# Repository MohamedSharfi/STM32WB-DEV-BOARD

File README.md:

# STM32 Development Breadboard Prototype 
This repository contains the schematic, PCB design, and documentation for an STM32-based development prototype designed for breadboard testing and prototyping.

## Project Status
     Schematic    :  100% Complete
     PCB Design   :  100% Complete
     Documentation:  100% Complete

## Table of Contents
Overview
Features
Getting Started
Project Files
Documentation
Contributing
License
Overview
This project aims to provide a robust STM32 development environment optimized for breadboard prototyping. It's ideal for my next projects development & testing.

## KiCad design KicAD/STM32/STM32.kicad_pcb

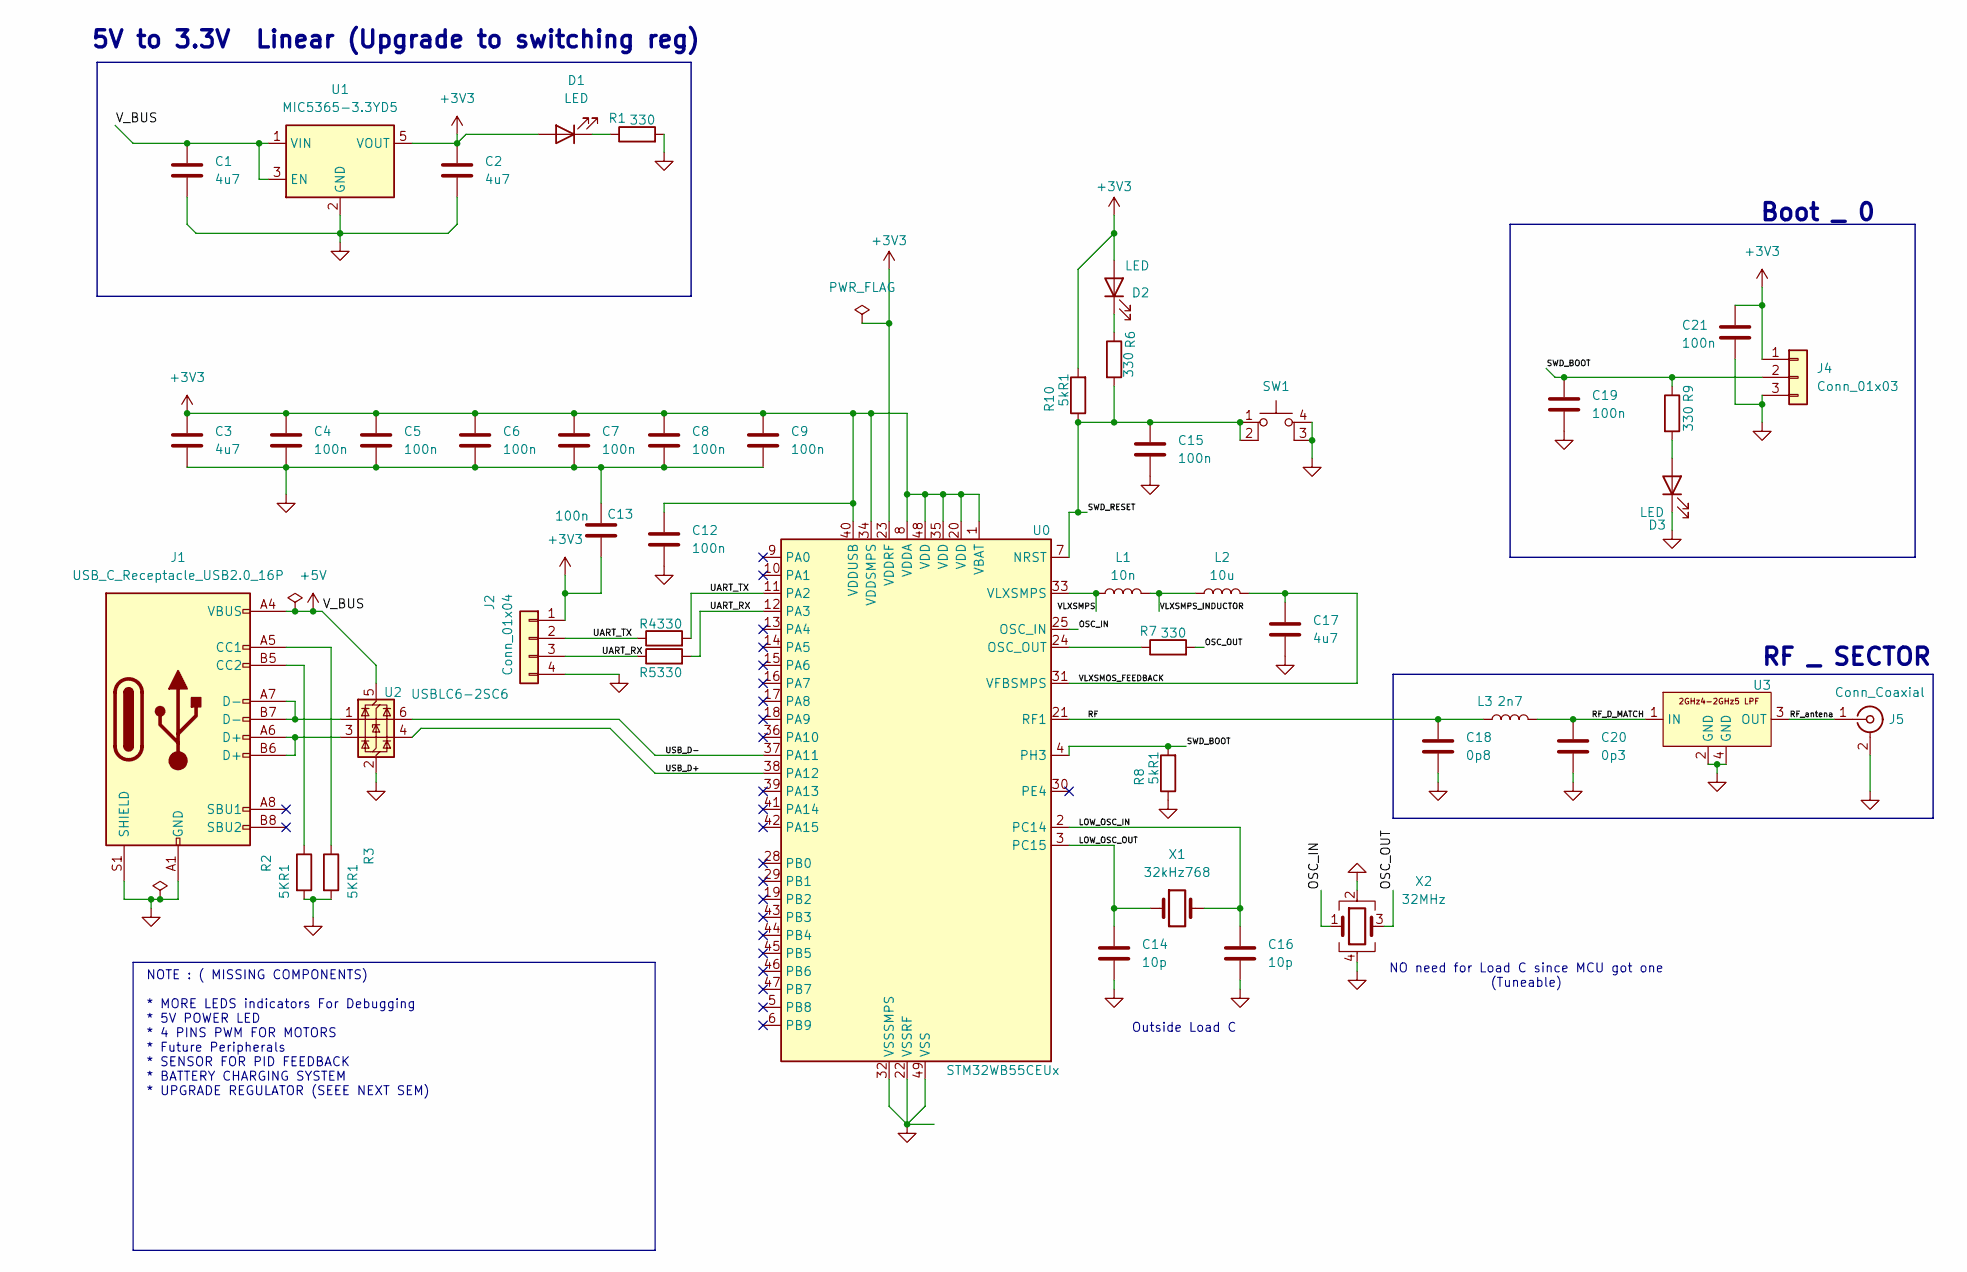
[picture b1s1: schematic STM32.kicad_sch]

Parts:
C1, C2, C3, C17: 4u7; C_0603_1608Metric
C4, C5, C6, C7, C8, C9, C12, C13, C15, C19, C21: 100n; C_0402_1005Metric
C14: 10p; C_0402_1005Metric
C16: 10p; C_0402_1005Metric_Pad0.74x0.62mm_HandSolder
C18: 0p8; C_0402_1005Metric
C20: 0p3; L_0402_1005Metric
D1, D2, D3: LED; LED_0402_1005Metric
J1: USB_C_Receptacle_USB2.0_16P; USB_C_Receptacle_GCT_USB4105-xx-A_16P_TopMnt_Horizontal
J2: Conn_01x04; Molex_PicoBlade_53048-0410_1x04_P1.25mm_Horizontal
J4: Conn_01x03; PinHeader_1x03_P2.54mm_Vertical
J5: Conn_Coaxial; U.FL_Hirose_U.FL-R-SMT-1_Vertical
L1: 10n; L_0402_1005Metric
L2: 10u; L_0805_2012Metric
L3: 2n7; L_0402_1005Metric
R1, R4, R5, R6, R7, R9: 330; R_0402_1005Metric
R2, R3: 5KR1; R_0402_1005Metric
R8, R10: 5kR1; R_0402_1005Metric
SW1: SW_MEC_5E; TS18-5-25-SL-260-SMT-TR
U0: STM32WB55CEUx; QFN-48-1EP_7x7mm_P0.5mm_EP5.6x5.6mm; Part Number STM32WB55CEU6
U1: MIC5365-3.3YD5; SOT-23-5; Part Number MIC5365-3.3YD5-TR
U2: USBLC6-2SC6; SOT-23-6; Part Number USBLC6-2SC6
U3: DLF162500LT-5028A1; Part Number DLF162500LT-5028A1
X1: 32kHz768; Crystal_SMD_2012-2Pin_2.0x1.2mm; Part Number NX2012SA-32.768K-STD-MUB-1
X2: 32MHz; Crystal_SMD_2016-4Pin_2.0x1.6mm; Part Number NX2016SA-32M-EXS00A-CS06465

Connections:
+3V3: C2.1, C3.1, C4.1, C5.1, C6.1, C7.1, C8.1, C9.1, C12.1, C13.2, C21.1, D1.2 (A), D2.2 (A), J2.1, J4.1, R10.2, U0.1 (VBAT), U0.8 (VDDA), U0.20 (VDD), U0.23 (VDDRF), U0.34 (VDDSMPS), U0.35 (VDD), U0.40 (VDDUSB), U0.48 (VDD), U1.5 (VOUT)
+5V: C1.1, J1.A4 (VBUS), J1.A9 (VBUS), J1.B4 (VBUS), J1.B9 (VBUS), U1.1 (VIN), U1.3 (EN), U2.5 (VBUS)
/LOW_OSC_IN: C16.1, U0.2 (PC14), X1.2
/LOW_OSC_OUT: C14.1, U0.3 (PC15), X1.1
/OSC_IN: U0.25 (OSC_IN), X2.1
/OSC_OUT: R7.2, X2.3
/RF: C18.1, L3.1, U0.21 (RF1)
/RF_D_MATCH: C20.1, L3.2, U3.1 (IN)
/RF_antena: J5.1 (In), U3.3 (OUT)
/SWD_BOOT: C19.1, J4.2, R8.2, R9.1, U0.4 (PH3)
/SWD_RESET: C15.1, R6.2, R10.1, SW1.1, SW1.2, U0.7 (NRST)
/UART_RX: J2.3, R5.1, R5.2, U0.12 (PA3)
/UART_TX: J2.2, R4.1, R4.2, U0.11 (PA2)
/USB_D+: U0.38 (PA12), U2.4 (I/O2)
/USB_D-: U0.37 (PA11), U2.6 (I/O1)
/VLXSMOS_FEEDBACK: C17.1, L2.2, U0.31 (VFBSMPS)
/VLXSMPS: L1.1, U0.33 (VLXSMPS)
/VLXSMPS_INDUCTOR: L1.2, L2.1
GND: C1.2, C2.2, C3.2, C4.2, C5.2, C6.2, C7.2, C8.2, C9.2, C12.2, C13.1, C14.2, C15.2, C16.2, C17.2, C18.2, C19.2, C20.2, C21.2, D3.1 (K), J1.A1 (GND), J1.A12 (GND), J1.B1 (GND), J1.B12 (GND), J1.S1 (SHIELD), J2.4, J4.3, J5.2 (Ext), R1.2, R2.2, R3.2, R8.1, SW1.3 (K), SW1.4 (A), U0.22 (VSSRF), U0.32 (VSSSMPS), U0.49 (VSS), U1.2 (GND), U2.2 (GND), U3.2 (GND), U3.4 (GND), X2.2, X2.4
unnamed: D1.1 (K), R1.1
unnamed: D2.1 (K), R6.1
unnamed: D3.2 (A), R9.2
unnamed: J1.A5 (CC1), R3.1
unnamed: J1.B5 (CC2), R2.1
unnamed: J1.A6 (D+), J1.B6 (D+), U2.3 (I/O2)
unnamed: J1.A7 (D-), J1.B7 (D-), U2.1 (I/O1)
unnamed: R7.1, U0.24 (OSC_OUT)

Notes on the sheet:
5V to 3.3V Linear (Upgrade to switching reg)
RF _ SECTOR
NOTE : ( MISSING COMPONENTS) * MORE LEDS indicators For Debugging * 5V POWER LED * 4 PINS PWM FOR MOTORS * Future Peripherals * SENSOR FOR PID FEEDBACK * BATTERY CHARGING SYSTEM * UPGRADE REGULATOR (SEEE NEXT SEM)
NO need for Load C since MCU got one (Tuneable)
Boot _ 0
Outside Load C

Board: 2 copper layers, 46 parts (0 on the bottom side), 27 nets, no tracks yet.

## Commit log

2024-12-01 Upload
2024-12-06 LastUpdateBeforePrint
    prepare for documentation and verifications
2024-12-06 folder
2024-12-09 update doc
2024-12-09 Doc update 100%
2025-02-19 TestBoard Finilizing
